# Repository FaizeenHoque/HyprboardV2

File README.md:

# HyprboardV2

> The RP2040-based dev board that actually got finished — unlike its predecessor.

HyprboardV2 is a compact, RP2040-based development board and the completed successor to the original HyprboardV1 (which never saw the light of day). Built for makers who want a capable, open-source board without the corporate overhead.

---

## Schematic

---

## PCB

---

## Renders

---

# Bill of Materials (BOM)

Manufactured by [JLCPCB](https://jlcpcb.com) · PCB Qty: 5 · Est. Total: **$51.7** (+ PCBA)

> Parts marked **Extended** may incur an additional setup fee at JLCPCB.  
> Headers (J2, J3, J4) are through-hole and excluded from SMT assembly — solder manually.

---

## Passives

| Designator | Value | Footprint | JLCPCB # | Qty | Type |
|---|---|---|---|---|---|
| C1, C2–C9, C11, C12, C17 | 100nF | 0402 | [C1525](https://jlcpcb.com/partdetail/1877-CL05B104KO5NNNC/C1525) | 60 | Basic |
| C10 | 1µF | 0402 | [C52923](https://jlcpcb.com/partdetail/53938-CL05A105KA5NQNC/C52923) | 5 | Basic |
| C13, C14 | 10µF | 0603 | [C19702](https://jlcpcb.com/partdetail/20411-CL10A106KP8NNNC/C19702) | 10 | Basic |
| C15, C16 | 33pF | 0603 | [C1663](https://jlcpcb.com/partdetail/2015-CL10C330JB8NNNC/C1663) | 10 | Basic |
| R1, R2 | 5.1kΩ | 0402 | [C25905](https://jlcpcb.com/partdetail/26648-0402WGF5101TCE/C25905) | 10 | Basic |
| R3, R4 | 27Ω | 0402 | [C25100](https://jlcpcb.com/partdetail/25843-0402WGF270JTCE/C25100) | 22 | Extended |
| R5, R6 | 1kΩ | 0402 | [C11702](https://jlcpcb.com/partdetail/12256-0402WGF1001TCE/C11702) | 10 | Basic |
| R7 | 10kΩ | 0402 | [C25744](https://jlcpcb.com/partdetail/26487-0402WGF1002TCE/C25744) | 5 | Basic |

## ICs & Active Components

| Designator | Part | Package | JLCPCB # | Qty | Type |
|---|---|---|---|---|---|
| U1 | RP2040 | QFN-56 (7×7mm) | [C2040](https://jlcpcb.com/partdetail/RaspberryPi-RP2040/C2040) | 5 | Extended |
| U2 | MCP1700T-3302E/TT (3.3V LDO) | SOT-23 | [C39051](https://jlcpcb.com/partdetail/MicrochipTech-MCP1700T_3302ETT/C39051) | 5 | Extended |
| U4 | W25Q16JVUXIQ (16Mbit Flash) | USON-8 (2×3mm) | [C2843335](https://jlcpcb.com/partdetail/WinbondElec-W25Q16JVUXIQ/C2843335) | 5 | Extended |
| Y1 | 12MHz Crystal | SMD 3225-4P | [C481407](https://jlcpcb.com/partdetail/NDK-NX3225GA_12MHZ_STD_CRG2/C481407) | 5 | Extended |

## Connectors & Switches

| Designator | Part | Package | JLCPCB # | Qty | Type | Notes |
|---|---|---|---|---|---|---|
| J1 | USB-C Receptacle (USB 2.0, 14P) | SMD Right-Angle | [C165948](https://jlcpcb.com/partdetail/Korean_HropartsElec-TYPE_C_31_M12/C165948) | 5 | Extended | |
| J2, J3 | 1×20 Pin Header, 2.54mm | Through-hole | [C50981](https://jlcpcb.com/partdetail/51993-2_54_1_20P/C50981) | — | Extended | **Solder manually** |
| J4 | 1×3 Pin Header, 2.54mm | Through-hole | [C49257](https://jlcpcb.com/partdetail/50265-2_54_1_3P/C49257) | — | Extended | **Solder manually** |
| SW1 | Tactile Switch, SPST-NO | SMD 4×3mm | [C720477](https://jlcpcb.com/partdetail/XUNPU-TS_1088AR02016/C720477) | 5 | Basic | |

---

## Getting Started

### Flashing Firmware

The Hyprboard V2 uses the **RP2040** microcontroller. It supports the
**Raspberry Pi Pico SDK**, **MicroPython**, and **CircuitPython**.

#### Entering Bootloader Mode (BOOTSEL)

The board has one button (SW1) which serves as the BOOTSEL button.

1. Hold **SW1**
2. Plug in USB-C
3. Release **SW1**
4. The board will appear as a USB drive called `RPI-RP2`
5. Drag and drop your `.uf2` firmware file onto it
6. The board reboots and runs your firmware automatically

#### Toolchain Options

| Option | Best For | Link |
|---|---|---|
| Pico SDK (C/C++) | Performance, low-level control | [Getting Started Guide](https://datasheets.raspberrypi.com/pico/getting-started-with-pico.pdf) |
| MicroPython | Rapid prototyping | [micropython.org](https://micropython.org/download/RPI_PICO/) |
| CircuitPython | Beginner friendly | [circuitpython.org](https://circuitpython.org/board/raspberry_pi_pico/) |

### Hardware Notes

- **Flash:** 16Mbit (2MB) W25Q16 external flash via QSPI
- **Crystal:** 12MHz — configure your SDK clock accordingly
- **Power:** 3.3V via MCP1700T LDO, input from USB-C (5V)
- **USB:** USB 2.0 Full Speed via USB-C (J1)

---

## Notes

- **R3, R4 (27Ω):** USB D+/D− series resistors. Value is correct per RP2040 hardware design guide.
- **U4 Flash mismatch:** BOM specifies `W25Q16JVZPIQTR`; JLCPCB substituted `W25Q16JVUXIQ` (same die, different package variant — USON-8 vs WSON-8). Verify footprint compatibility before ordering.
- **C1 warning:** JLCPCB flags comment mismatch (part number vs value). This is cosmetic — the part is correct.
- Re-match BOM on JLCPCB if more than 24 hours have passed since last match, as stock and pricing change.

---

## 📜 License

Hardware licensed under [CERN-OHL-P v2](https://ohwr.org/cern_ohl_p_v2.txt)

---

## 🙏 Acknowledgements

Inspired by the failure that was HyprboardV1. Thanks for nothing, V1.

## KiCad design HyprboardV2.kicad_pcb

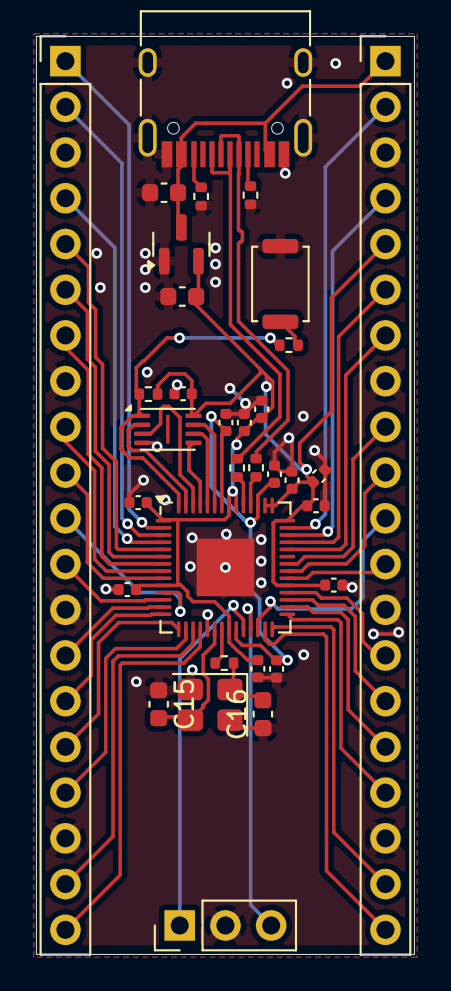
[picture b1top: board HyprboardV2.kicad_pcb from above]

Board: 2 copper layers, 21.0 x 51.0 mm, 33 parts (0 on the bottom side), 52 nets.

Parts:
C1, C2, C3, C4, C5, C6, C7, C8, C9, C11, C12, C17: 0.1uF; C_0402_1005Metric
C10: 1uF; C_0402_1005Metric
C13, C14: 10uF; C_0603_1608Metric
C15, C16: 33pF; C_0603_1608Metric
J1: USB_C_Receptacle_USB2.0_14P; USB_C_Receptacle_HRO_TYPE-C-31-M-12
J2, J3: Conn_01x20; PinHeader_1x20_P2.54mm_Vertical
J4: Conn_01x03; PinHeader_1x03_P2.54mm_Vertical
R1, R2: 5.1K; R_0402_1005Metric
R3, R4: 27; R_0402_1005Metric
R5, R6: 1K; R_0402_1005Metric
R7: 10K; R_0402_1005Metric
SW1: SW_Push; SW_Push_SPST_NO_Alps_SKRK
U1: RP2040; QFN-56-1EP_7x7mm_P0.4mm_EP3.2x3.2mm
U2: MCP1700x-330xxTT; SOT-23
U4: W25Q16JVZPIQ TR; Winbond_USON-8-1EP_3x2mm_P0.5mm_EP0.2x1.6mm
Y1: 12 MHz; Crystal_SMD_3225-4Pin_3.2x2.5mm

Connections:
+1V1: C10.1, C11.1, C12.1, U1.23 (DVDD), U1.45 (VREG_VOUT), U1.50 (DVDD)
+3V3: C1.1, C2.1, C3.1, C4.1, C5.1, C6.1, C7.1, C8.1, C9.1, C14.1, C17.1, J3.5, R7.1, U1.1 (IOVDD), U1.10 (IOVDD), U1.22 (IOVDD), U1.33 (IOVDD), U1.42 (IOVDD), U1.43 (ADC_AVDD), U1.44 (VREG_VIN), U1.48 (USB_VDD), U1.49 (IOVDD), U2.2 (VO), U4.8 (VCC)
GND: C1.2, C2.2, C3.2, C4.2, C5.2, C6.2, C7.2, C8.2, C9.2, C10.2, C11.2, C12.2, C13.2, C14.2, C15.1, C16.1, C17.2, J1.A1 (GND), J1.A12 (GND), J1.B1 (GND), J1.B12 (GND), J1.S1 (SHIELD), J2.3, J2.8, J2.13, J2.18, J3.3, J3.8, J3.13, J3.18, J4.2, R1.2, R2.2, SW1.1, U1.19 (TESTEN), U1.57 (GND), U2.1 (GND), U4.4 (GND), Y1.2 (G), Y1.4 (G)
GPIO0: J2.1, U1.2 (GPIO0)
GPIO1: J2.2, U1.3 (GPIO1)
GPIO2: J2.4, U1.4 (GPIO2)
GPIO3: J2.5, U1.5 (GPIO3)
GPIO4: J2.6, U1.6 (GPIO4)
GPIO5: J2.7, U1.7 (GPIO5)
GPIO6: J2.9, U1.8 (GPIO6)
GPIO7: J2.10, U1.9 (GPIO7)
GPIO8: J2.11, U1.11 (GPIO8)
GPIO9: J2.12, U1.12 (GPIO9)
GPIO10: J2.14, U1.13 (GPIO10)
GPIO11: J2.15, U1.14 (GPIO11)
GPIO12: J2.16, U1.15 (GPIO12)
GPIO13: J2.17, U1.16 (GPIO13)
GPIO14: J2.19, U1.17 (GPIO14)
GPIO15: J2.20, U1.18 (GPIO15)
GPIO16: J3.20, U1.27 (GPIO16)
GPIO17: J3.19, U1.28 (GPIO17)
GPIO18: J3.17, U1.29 (GPIO18)
GPIO19: J3.16, U1.30 (GPIO19)
GPIO20: J3.15, U1.31 (GPIO20)
GPIO21: J3.14, U1.32 (GPIO21)
GPIO22: J3.12, U1.34 (GPIO22)
GPIO23: J3.10, U1.35 (GPIO23)
GPIO24: J3.9, U1.36 (GPIO24)
GPIO26_ADC0: J3.7, U1.38 (GPIO26/ADC0)
GPIO27_ADC1: J3.6, U1.39 (GPIO27/ADC1)
GPIO28_ADC2: J3.4, U1.40 (GPIO28/ADC2)
GPIO29_ADC3: J3.2, U1.41 (GPIO29/ADC3)
unnamed: C16.2, R5.1, Y1.1
unnamed: J1.A5 (CC1), R2.1
unnamed: J1.B5 (CC2), R1.1
unnamed: R6.1, SW1.2
unnamed: R3.2, U1.46 (USB_DM)
unnamed: R4.2, U1.47 (USB_DP)
QSPI_SCLK: U1.52 (QSPI_SCLK), U4.6 (CLK)
QSPI_SD0: U1.53 (QSPI_SD0), U4.5 (DI/IO_{0})
QSPI_SD1: U1.55 (QSPI_SD1), U4.2 (DO/IO_{1})
QSPI_SD2: U1.54 (QSPI_SD2), U4.3 (~WP/IO_{2})
QSPI_SD3: U1.51 (QSPI_SD3), U4.7 (~HOLD/~RESET/IO_{3})
QSPI_SS: R6.2, R7.2, U1.56 (~QSPI_SS), U4.1 (~CS)
RUN: J3.11, U1.26 (RUN)
SWCLK: J4.1, U1.24 (SWCLK)
SWD: J4.3, U1.25 (SWDIO)
USB_D+: J1.A6 (D+), J1.B6 (D+), R4.1
USB_D-: J1.A7 (D-), J1.B7 (D-), R3.1
VBUS: C13.1, J1.A4 (VBUS), J1.A9 (VBUS), J1.B4 (VBUS), J1.B9 (VBUS), J3.1, U2.3 (VI)
XIN: C15.2, U1.20 (XIN), Y1.3
XOUT: R5.2, U1.21 (XOUT)

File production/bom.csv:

Designator,Footprint,Quantity,Value,LCSC Part #
"C1, C11, C12, C17, C2, C3, C4, C5, C6, C7, C8, C9",0402,12,0.1uF,
C10,0402,1,1uF,
"C13, C14",0603,2,10uF,
"C15, C16",0603,2,33pF,
J1,USB_C_Receptacle_HRO_TYPE-C-31-M-12,1,USB_C_Receptacle_USB2.0_14P,
"J2, J3",PinHeader_1x20_P2.54mm_Vertical,2,Conn_01x20,
J4,PinHeader_1x03_P2.54mm_Vertical,1,Conn_01x03,
"R1, R2",0402,2,5.1K,
"R3, R4",0402,2,27,
"R5, R6",0402,2,1K,
R7,0402,1,10K,
SW1,SW_Push_SPST_NO_Alps_SKRK,1,SW_Push,
U1,QFN-56-1EP_7x7mm_P0.4mm_EP3.2x3.2mm,1,RP2040,
U2,SOT-23,1,MCP1700x-330xxTT,
U4,Winbond_USON-8-1EP_3x2mm_P0.5mm_EP0.2x1.6mm,1,W25Q16JVZPIQ TR,
Y1,Crystal_SMD_3225-4Pin_3.2x2.5mm,1,12 MHz,

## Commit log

2026-03-06 initial
2026-03-06 finished up with the decoupling capacitors, finished up with the USB
2026-03-06 Crystal Oscilator, Flash Memory done! Started working on the breakout for GPIO pins
2026-03-06 Finished up the schematic
2026-03-06 Changed the stuff Flash and USB components, 1/3rd positioned the components
2026-03-06 Position 2/3rd of the components
2026-03-07 Almost dont placements, ill start routing next and do the rest simulatneously
2026-03-07 DONE WITH THE ROUTINGGGgit add .! checkout stasis's journal for info
2026-03-07 Added some renders, and added some text to the boarddddgit add .!
2026-03-07 Create README.md for HyprboardV2
    Added initial README for HyprboardV2 with features, schematic, PCB, renders, BOM, getting started guide, license, and acknowledgements.
2026-03-07 Remove BOM file reference from README
    Removed reference to the full BOM file location.
2026-03-08 production files
2026-03-15 Revise README with features and BOM details
    Updated features, BOM, and added passive components section in README.
2026-03-15 Revise section headers and BOM pricing
    Updated section headers and BOM cost in README.md.
2026-03-20 Modify BOM with part numbers and values
    Updated component values and added LCSC part numbers.
2026-03-20 Update README with firmware flashing instructions
    Added instructions for flashing firmware and toolchain options for the Hyprboard V2.
